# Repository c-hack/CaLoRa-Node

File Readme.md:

# CaLoRa-Node
## c-hack.de and surasto.de 2020 

This LoRaWAN node is designed to run for long time on a battery.
It uses an external RTC (DS1337) with alarm function to enable or disable the complete power supply by switching a P-MOS FET.
This is the deepest sleep possible.

It uses an Atmel ATMega328 with the Arduino-UNO bootloader.
The LoRAWAN is implemented with an HopeRF RFM95W module.
The board implements some grove compatible connectors wuth I2C and analog inputs of the MCU.

We use the [lmic](https://github.com/matthijskooijman/arduino-lmic "lmic") software library for now but will add a wrapper to make it simpler.

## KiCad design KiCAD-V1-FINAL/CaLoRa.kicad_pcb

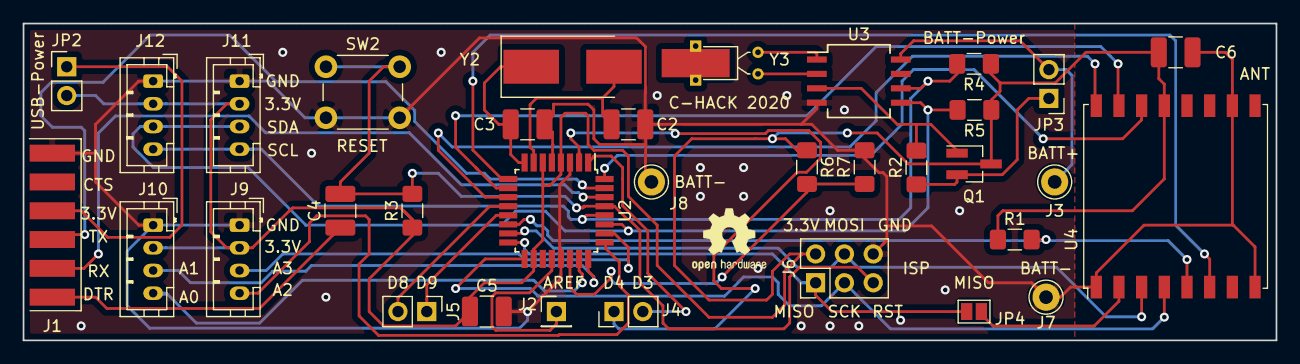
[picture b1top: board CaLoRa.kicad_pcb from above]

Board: 2 copper layers, 110.5 x 27.9 mm, 34 parts (0 on the bottom side), 35 nets.

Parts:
C2, C3: 22p; C_1210_3225Metric_Pad1.42x2.65mm_HandSolder
C4, C5, C6: 100n; C_1210_3225Metric_Pad1.42x2.65mm_HandSolder
J1: Conn_01x06_Male; TestPoint_Pad_6x1.5x4.0mm
J2: Conn_01x01_Male; PinHeader_1x01_P2.54mm_Vertical
J3, J7, J8: Screw_Terminal_01x01; Pin_D1.0mm_L10.0mm_LooseFit
J4, J5: Conn_01x02_Male; PinHeader_1x02_P2.54mm_Vertical
J6: AVR-ISP-6; PinHeader_2x03_P2.54mm_Vertical
J9, J10, J11, J12: Conn_01x04_Male; JST_PH_B4B-PH-K_1x04_P2.00mm_Vertical
JP2, JP3: Jumper; PinHeader_1x02_P2.54mm_Vertical
JP4: SolderJumper_2_Open; SolderJumper-2_P1.3mm_Open_Pad1.0x1.5mm
Q1: Q_PMOS_GSD; SOT-23_Handsoldering
R1, R3, R4, R5: 10k; R_1206_3216Metric_Pad1.42x1.75mm_HandSolder
R2: 22k; R_1206_3216Metric_Pad1.42x1.75mm_HandSolder
R6, R7: 100k; R_1206_3216Metric_Pad1.42x1.75mm_HandSolder
SW2: SW_Push_Dual; SW_PUSH_6mm_H5mm
U2: ATmega328-AU; TQFP-32_7x7mm_P0.8mm
U3: DS1337; SO-8_5.3x6.2mm_P1.27mm
U4: RFM95W-868S2; HOPERF_RFM9XW_SMD
Y2: 16MHz; Crystal_SMD_7050-2Pin_7.0x5.0mm_HandSoldering
Y3: 32kHz; Crystal_DS26_D2.0mm_L6.0mm_Horizontal_1EP_style2

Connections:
+3V3: C5.1, C6.1, J6.2, J9.2, J10.2, J11.2, J12.2, JP2.2, Q1.3, R1.1, R3.1, R4.1, R5.1, R6.1, U2.4, U2.6, U2.18, U4.13
+BATT: J3.1, JP3.2, U3.8
A0: J10.4, U2.23
A1: J10.3, U2.24
A2: J9.4, U2.25
A3: J9.3, U2.26
DTR: C4.1, J1.1
GND: C2.2, C3.1, C5.2, C6.2, J1.6, J6.6, J7.1, J8.1, J9.1, J10.1, J11.1, J12.1, R7.2, SW2.2, U2.3, U2.5, U2.21, U3.4, U4.1, U4.8, U4.10
MISO: J6.1, JP4.1, U2.16
MOSI: J6.4, U2.15, U4.3
unnamed: C2.1, U2.7, Y2.2
unnamed: C3.2, U2.8, Y2.1
unnamed: C4.2, J6.5, R3.2, SW2.1, U2.29
unnamed: J1.4, JP2.1
unnamed: J2.1, U2.20
unnamed: J4.1, U2.2
unnamed: J4.2, U2.1
unnamed: J5.1, U2.13
unnamed: J5.2, U2.12
unnamed: JP3.1, Q1.2, R2.1
unnamed: JP4.2, U4.2
unnamed: Q1.1, R2.2, U3.3
unnamed: R6.2, R7.1, U2.22
unnamed: U2.9, U4.6
unnamed: U2.10, U4.15
unnamed: U2.11, U4.16
unnamed: U2.32, U4.14
unnamed: U3.1, Y3.1
unnamed: U3.2, Y3.2
RX: J1.2, U2.30
SCK: J6.3, U2.17, U4.4
SCL: J11.4, J12.4, R4.2, U2.28, U3.6
SDA: J11.3, J12.3, R5.2, U2.27, U3.5
SS: R1.2, U2.14, U4.5
TX: J1.3, U2.31

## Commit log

2020-08-28 readme added
2020-08-28 readme edited
2020-12-05 Errata added
2021-03-14 neue version
